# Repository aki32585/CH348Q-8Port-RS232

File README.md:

# CH348Q-8Port-RS232
  
CH348Qを使用した8ポートRS232変換ボード  
コネクタはRJ45、ピン配置はCisco互換

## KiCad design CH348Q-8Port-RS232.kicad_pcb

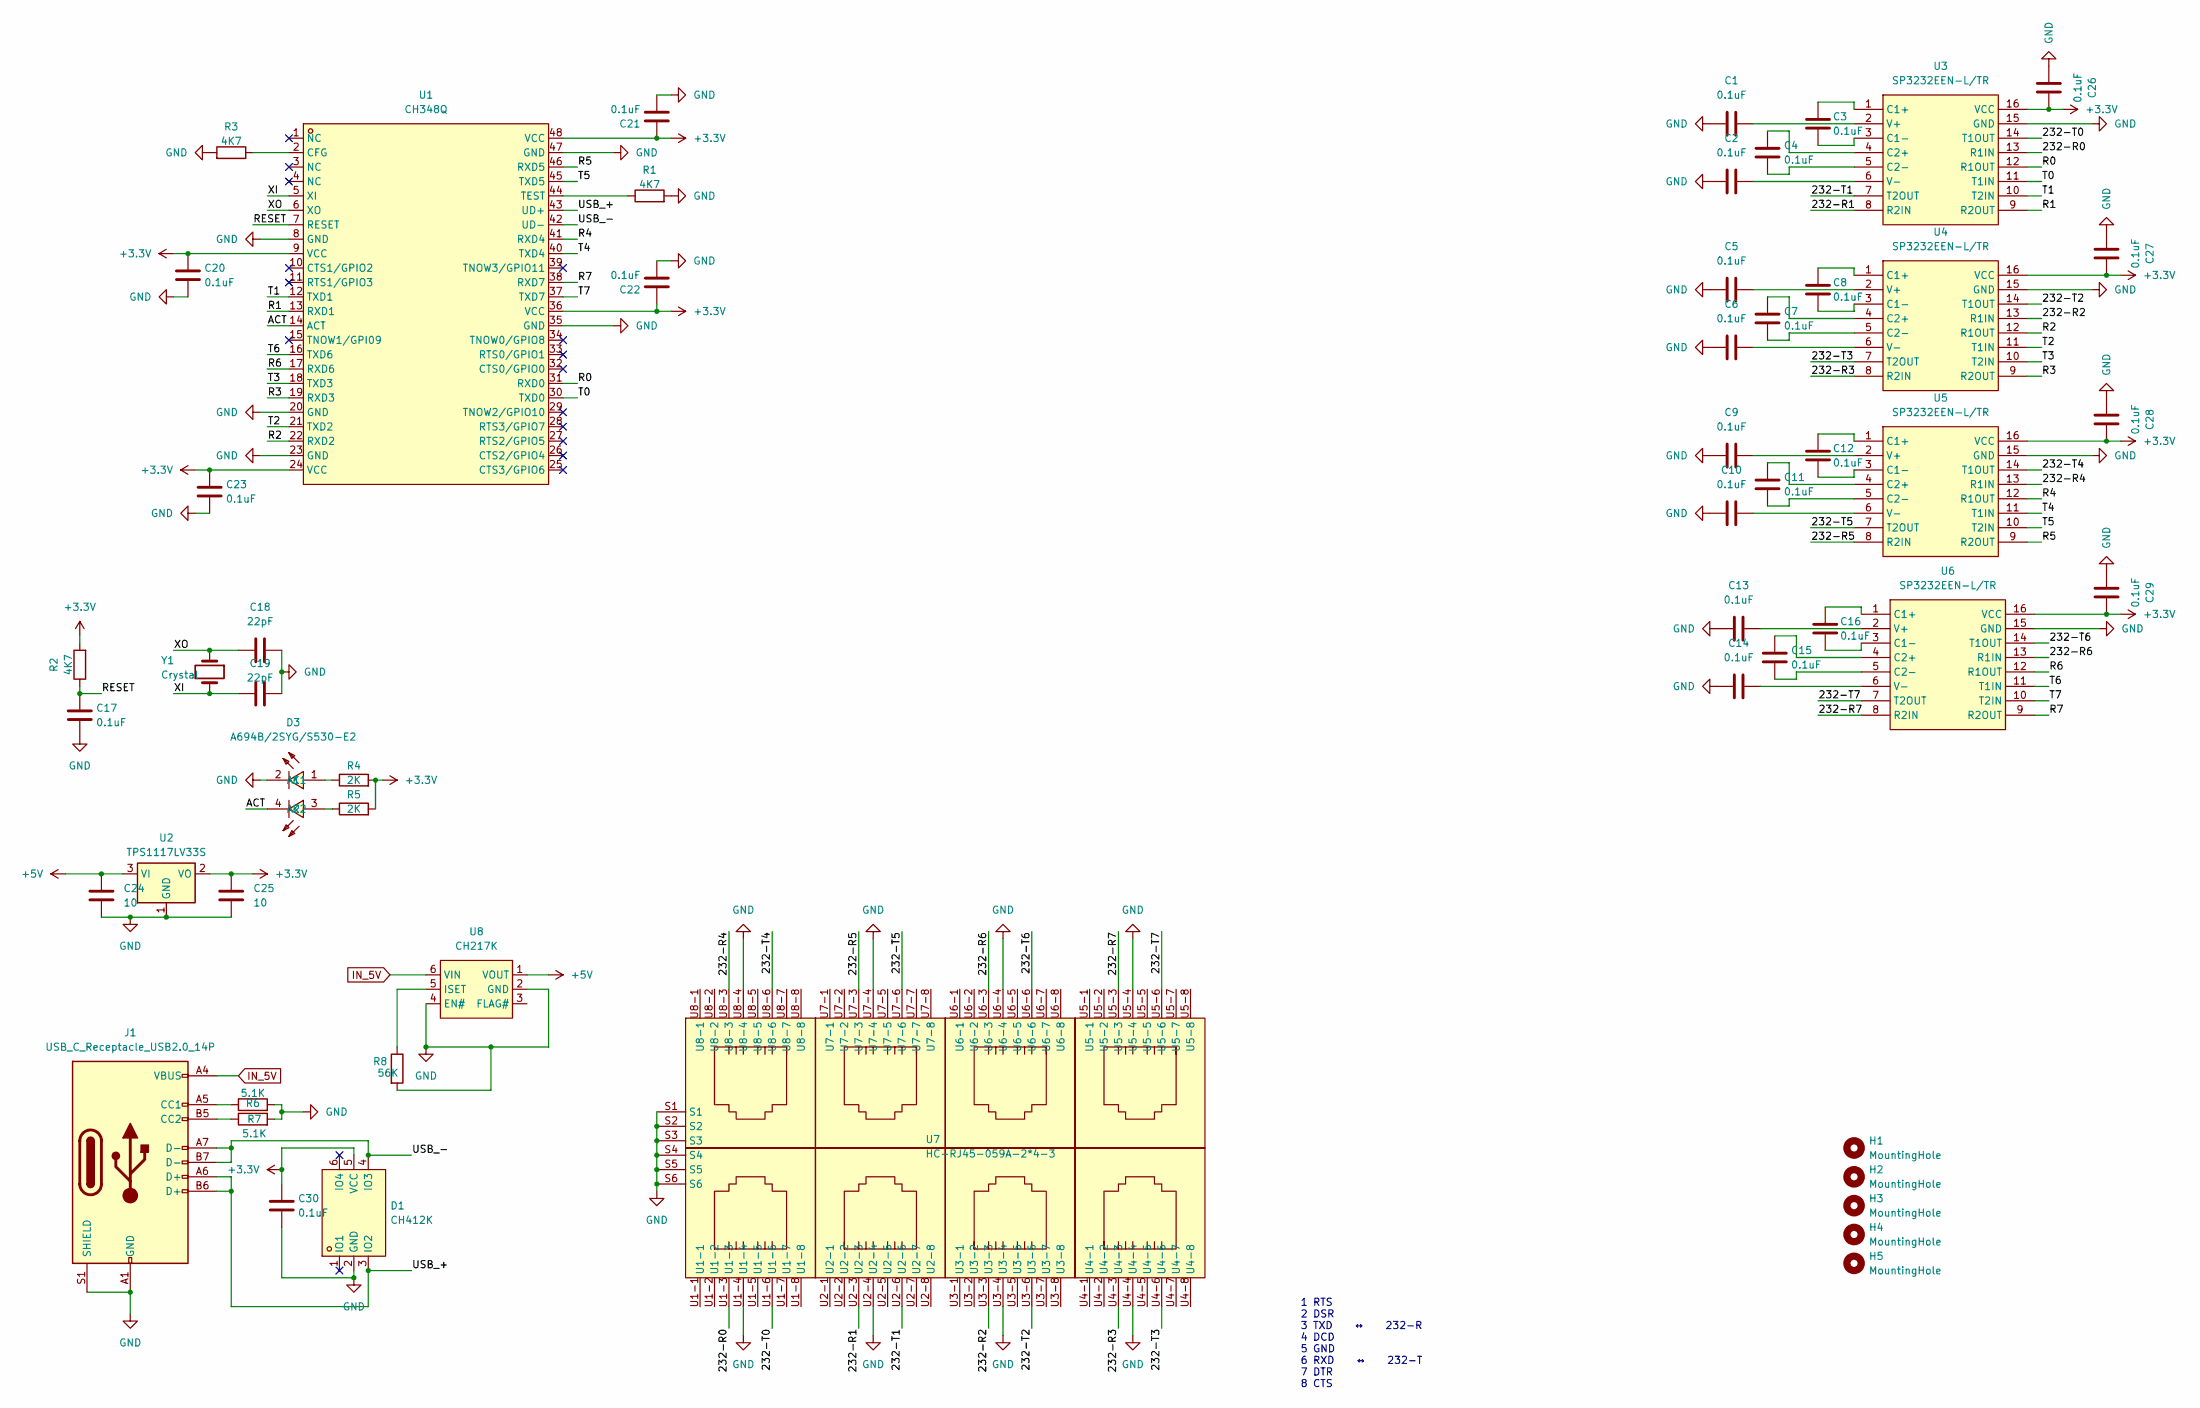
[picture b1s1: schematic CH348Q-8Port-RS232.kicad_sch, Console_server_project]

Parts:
C1, C2, C3, C4, C5, C6, C7, C8, C9, C10, C11, C12, C13, C14, C15, C16, C17, C20, C21, C22, C23, C26, C27, C28, C29, C30: 0.1uF; C_0603_1608Metric
C18, C19: 22pF; C_0603_1608Metric
C24, C25: 10; C_0603_1608Metric
D1: CH412K; SOT-363_L2.0-W1.3-P0.65-LS2.1-BR; LCSC Part C89184
D3: A694B/2SYG/S530-E2; LED-TH_A694B2SYGS530-E2; LCSC Part C93880
H1, H2, H3, H4: MountingHole; MountingHole_3.2mm_M3
H5: MountingHole; MountingHole_2.2mm_M2
J1: USB_C_Receptacle_USB2.0_14P; USB_C_Receptacle_GCT_USB4105-xx-A_16P_TopMnt_Horizontal
R1, R2, R3: 4K7; R_0603_1608Metric
R4, R5: 2K; R_0603_1608Metric
R6, R7: 5.1K; R_0603_1608Metric
R8: 56K; R_0603_1608Metric
U1: CH348Q; LQFP-48_L7.0-W7.0-P0.50-LS9.0-BL; LCSC Part C2979161
U2: TPS1117LV33S; SOT-223-3_TabPin2
U3, U4, U5, U6: SP3232EEN-L/TR; SOIC-16_L9.9-W3.9-P1.27-LS6.0-BL; LCSC Part C9378
U7: HC-RJ45-059A-2*4-3; RJ45-TH_R-RJ45R08P-8000; LCSC Part C3000220
U8: CH217K; SOT-23-6
Y1: Crystal; Crystal_HC49-U_Vertical

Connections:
+3.3V: C20.1, C21.1, C22.1, C23.1, C25.1, C26.1, C27.1, C28.1, C29.1, C30.1, D1.5 (VCC), R2.2, R4.2, R5.2, U1.9 (VCC), U1.24 (VCC), U1.36 (VCC), U1.48 (VCC), U2.2 (VO), U3.16 (VCC), U4.16 (VCC), U5.16 (VCC), U6.16 (VCC)
+5V: C24.1, U2.3 (VI), U8.1 (VOUT)
/232-R0: U3.13 (R1IN), U7.U1-3
/232-R1: U3.8 (R2IN), U7.U2-3
/232-R2: U4.13 (R1IN), U7.U3-3
/232-R3: U4.8 (R2IN), U7.U4-3
/232-R4: U5.13 (R1IN), U7.U8-3
/232-R5: U5.8 (R2IN), U7.U7-3
/232-R6: U6.13 (R1IN), U7.U6-3
/232-R7: U6.8 (R2IN), U7.U5-3
/232-T0: U3.14 (T1OUT), U7.U1-6
/232-T1: U3.7 (T2OUT), U7.U2-6
/232-T2: U4.14 (T1OUT), U7.U3-6
/232-T3: U4.7 (T2OUT), U7.U4-6
/232-T4: U5.14 (T1OUT), U7.U8-6
/232-T5: U5.7 (T2OUT), U7.U7-6
/232-T6: U6.14 (T1OUT), U7.U6-6
/232-T7: U6.7 (T2OUT), U7.U5-6
/ACT: D3.4 (K2), U1.14 (ACT)
/R0: U1.31 (RXD0), U3.12 (R1OUT)
/R1: U1.13 (RXD1), U3.9 (R2OUT)
/R2: U1.22 (RXD2), U4.12 (R1OUT)
/R3: U1.19 (RXD3), U4.9 (R2OUT)
/R4: U1.41 (RXD4), U5.12 (R1OUT)
/R5: U1.46 (RXD5), U5.9 (R2OUT)
/R6: U1.17 (RXD6), U6.12 (R1OUT)
/R7: U1.38 (RXD7), U6.9 (R2OUT)
/RESET: C17.1, R2.1, U1.7 (RESET)
/T0: U1.30 (TXD0), U3.11 (T1IN)
/T1: U1.12 (TXD1), U3.10 (T2IN)
/T2: U1.21 (TXD2), U4.11 (T1IN)
/T3: U1.18 (TXD3), U4.10 (T2IN)
/T4: U1.40 (TXD4), U5.11 (T1IN)
/T5: U1.45 (TXD5), U5.10 (T2IN)
/T6: U1.16 (TXD6), U6.11 (T1IN)
/T7: U1.37 (TXD7), U6.10 (T2IN)
/USB_+: D1.3 (IO2), J1.A6 (D+), J1.B6 (D+), U1.43 (UD+)
/USB_-: D1.4 (IO3), J1.A7 (D-), J1.B7 (D-), U1.42 (UD-)
/XI: C19.2, U1.5 (XI), Y1.2
/XO: C18.2, U1.6 (XO), Y1.1
GND: C1.2, C2.2, C5.2, C6.2, C9.2, C10.2, C13.2, C14.2, C17.2, C18.1, C19.1, C20.2, C21.2, C22.2, C23.2, C24.2, C25.2, C26.2, C27.2, C28.2, C29.2, C30.2, D1.2 (GND), D3.2 (K1), J1.A1 (GND), J1.A12 (GND), J1.B1 (GND), J1.B12 (GND), J1.S1 (SHIELD), R1.2, R3.2, R6.2, R7.2, R8.2, U1.8 (GND), U1.20 (GND), U1.23 (GND), U1.35 (GND), U1.47 (GND), U2.1 (GND), U3.15 (GND), U4.15 (GND), U5.15 (GND), U6.15 (GND), U7.S1, U7.S2, U7.S3, U7.S4, U7.S5, U7.S6, U7.U1-4, U7.U2-4, U7.U3-4, U7.U4-4, U7.U5-4, U7.U6-4, U7.U7-4, U7.U8-4, U8.2 (GND), U8.4 (EN#)
IN_5V: J1.A4 (VBUS), J1.A9 (VBUS), J1.B4 (VBUS), J1.B9 (VBUS), U8.6 (VIN)
unnamed: D3.1 (A1), R4.1
unnamed: D3.3 (A2), R5.1
unnamed: J1.A5 (CC1), R6.1
unnamed: J1.B5 (CC2), R7.1
unnamed: R3.1, U1.2 (CFG)
unnamed: R1.1, U1.44 (TEST)
unnamed: C3.1, U3.1 (C1+)
unnamed: C3.2, U3.3 (C1-)
unnamed: C4.1, U3.4 (C2+)
unnamed: C4.2, U3.5 (C2-)
unnamed: C1.1, U3.2 (V+)
unnamed: C2.1, U3.6 (V-)
unnamed: C8.1, U4.1 (C1+)
unnamed: C8.2, U4.3 (C1-)
unnamed: C7.1, U4.4 (C2+)
unnamed: C7.2, U4.5 (C2-)
unnamed: C5.1, U4.2 (V+)
unnamed: C6.1, U4.6 (V-)
unnamed: C12.1, U5.1 (C1+)
unnamed: C12.2, U5.3 (C1-)
unnamed: C11.1, U5.4 (C2+)
unnamed: C11.2, U5.5 (C2-)
unnamed: C9.1, U5.2 (V+)
unnamed: C10.1, U5.6 (V-)
unnamed: C16.1, U6.1 (C1+)
unnamed: C16.2, U6.3 (C1-)
unnamed: C15.1, U6.4 (C2+)
unnamed: C15.2, U6.5 (C2-)
unnamed: C13.1, U6.2 (V+)
unnamed: C14.1, U6.6 (V-)
unnamed: R8.1, U8.5 (ISET)

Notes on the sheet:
1 RTS 2 DSR 3 TXD ↔ 232-R 4 DCD 5 GND 6 RXD ↔ 232-T 7 DTR 8 CTS

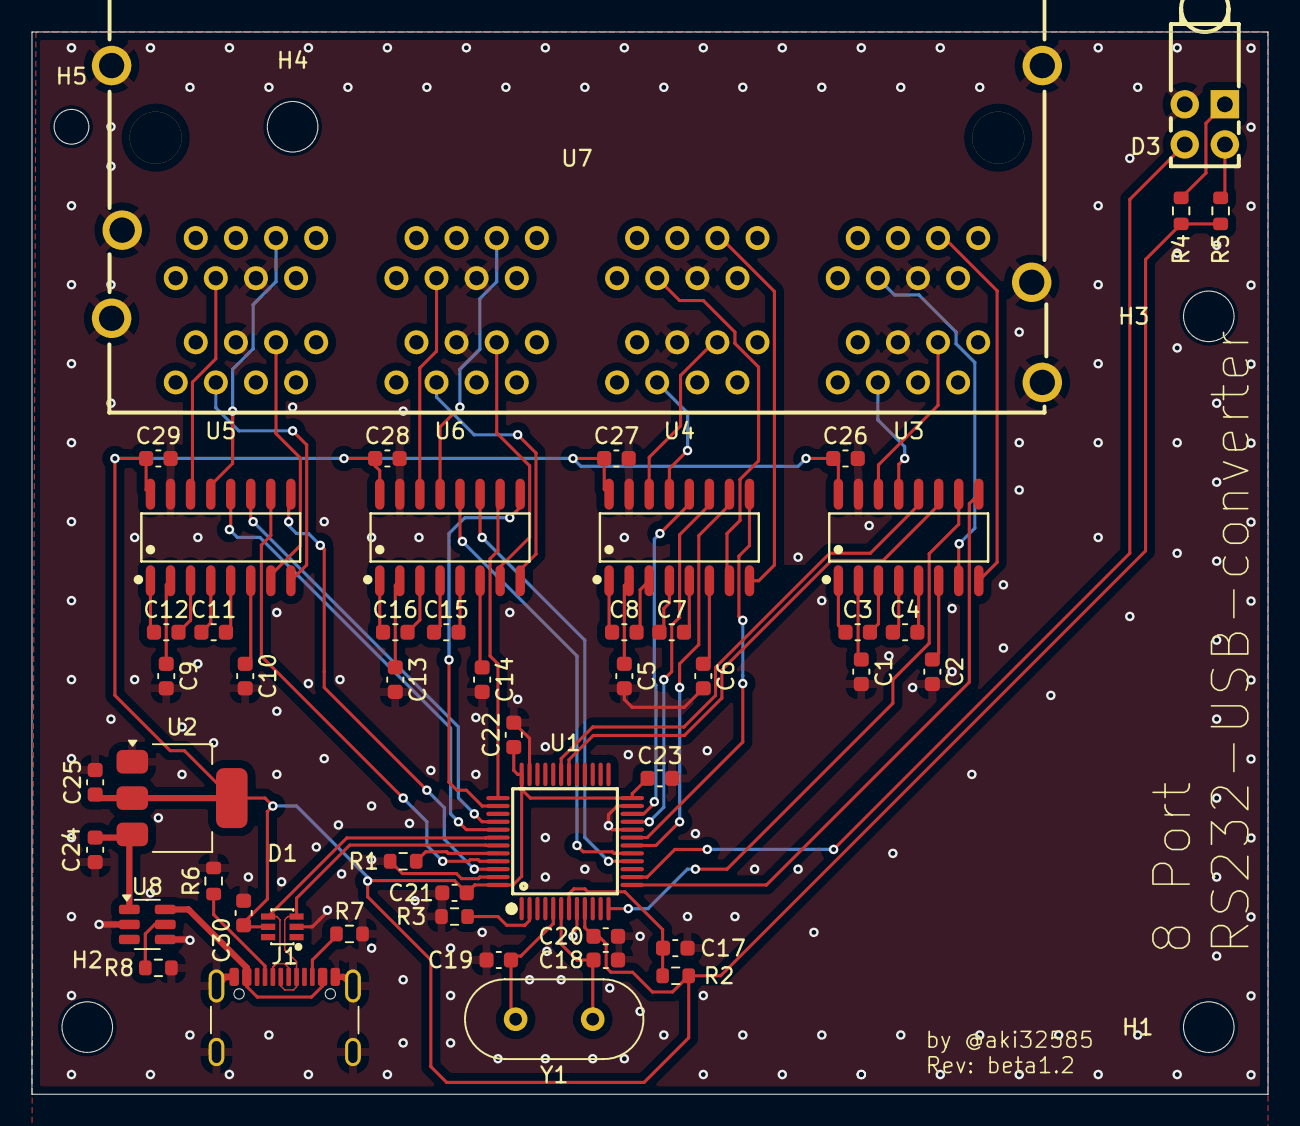
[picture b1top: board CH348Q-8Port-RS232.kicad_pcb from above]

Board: 2 copper layers, 78.2 x 67.2 mm, 55 parts (0 on the bottom side), 73 nets.

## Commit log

2026-06-03 add kicad project files
